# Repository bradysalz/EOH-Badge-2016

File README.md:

# EOH-Badge-2016
Badges made to hand out as a teaching exercise for the IEEE UIUC exhibit at Engineering Open House 2016. When you cover up the light sensor, the badges play along and flash to "Hail to the Orange". You can see a video of the build in action [here](https://www.youtube.com/watch?v=S4cmx-UWJ_Q&feature=youtu.be). This exhibit won second place in the "Just for Fun" category!

Special thanks to [David Mellis](http://web.media.mit.edu/~mellis/) for his [attiny library](https://github.com/damellis/attiny).

# Media

You can see a video of the exhibit in action, as well as IEEE's other exhibits [here](https://www.youtube.com/watch?v=S4cmx-UWJ_Q&feature=youtu.be).

Some excellent photos taken by Ray Chan during EOH [here](https://photos.google.com/share/AF1QipN_tZymQB7QjqU8kMJ0lrtPr13E5zKEWU58SieGECw1yZU4zlcl4fVr3wqzv2gzeQ?key=Mm0zcS1icEtFYU44bktMVk84OHpqdEVZcEROZm53)

# Bugs
- Orange and Blue LED are labeled backwards, whoops!
- The 500kOhm resistor is far too large, 50k would be much better. Typo from reading the datasheet, just makes the devices extremely sensitive. 
- First note is always wrong, probably need to re-read Timer init code
- Lanyard hole is slightly too small, +5-10 mils would be better
- My initials are covered up the battery cover (this one was actually intended)

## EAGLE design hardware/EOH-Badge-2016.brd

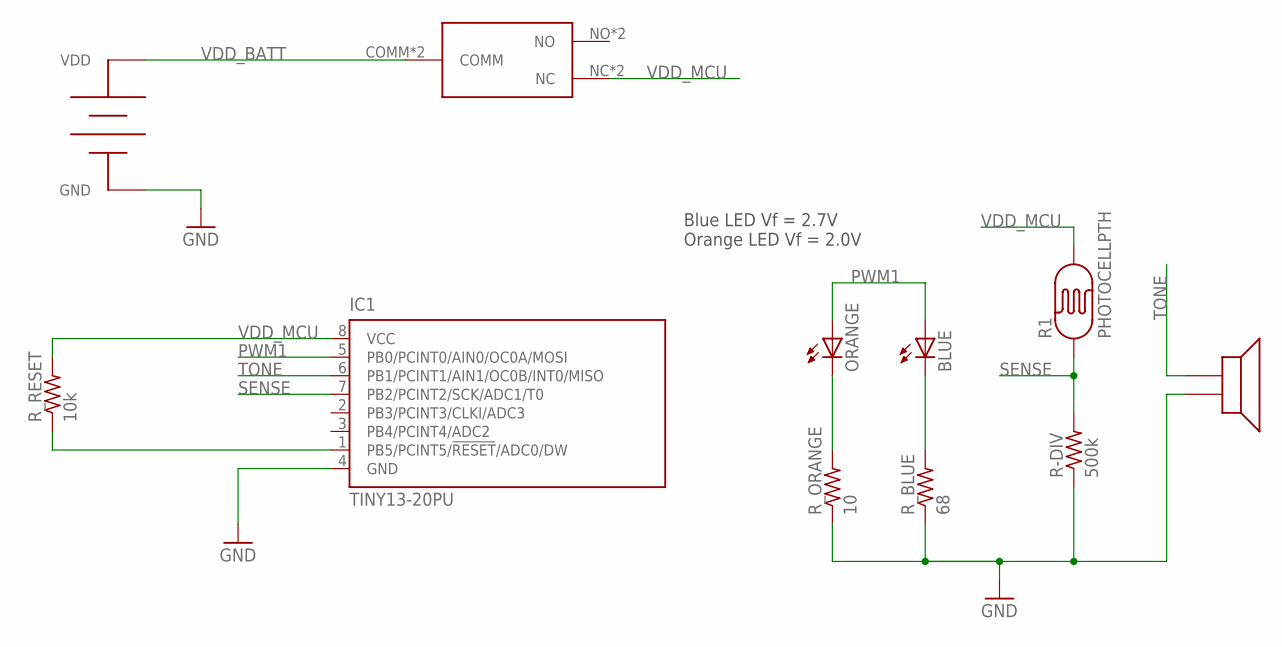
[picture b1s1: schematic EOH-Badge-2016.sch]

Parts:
BLUE: LED5MM
IC1: TINY13-20PU; DIL08
ORANGE: LED5MM
R1: PHOTOCELLPTH; PHOTOCELL
R-DIV: 500k; 0207/12
R_BLUE: 68; 0207/12
R_ORANGE: 10; 0207/12
R_RESET: 10k; 0207/12
U$1: MPD-BH32T-C; MPD-BC2032-E2
U$2: PIEZO; PS1240P02BT
U$3: EG1919-SW

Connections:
GND: IC1.4 (GND), R-DIV.1, R_BLUE.1, R_ORANGE.1, U$1.NEG (GND), U$2.GND
unnamed: IC1.1 (PB5/PCINT5/!RESET!/ADC0/DW), R_RESET.1
unnamed: ORANGE.K (C), R_ORANGE.2
unnamed: BLUE.K (C), R_BLUE.2
PWM1: BLUE.A, IC1.5 (PB0/PCINT0/AIN0/OC0A/MOSI), ORANGE.A
SENSE: IC1.7 (PB2/PCINT2/SCK/ADC1/T0), R1.1, R-DIV.2
TONE: IC1.6 (PB1/PCINT1/AIN1/OC0B/INT0/MISO), U$2.AUDIO
VDD_BATT: U$1.POS (VDD), U$3.COMM, U$3.COMM2 (COMM)
VDD_MCU: IC1.8 (VCC), R1.2, R_RESET.2, U$3.NC, U$3.NC2 (NC)

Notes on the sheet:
Blue LED Vf = 2.7V Orange LED Vf = 2.0V

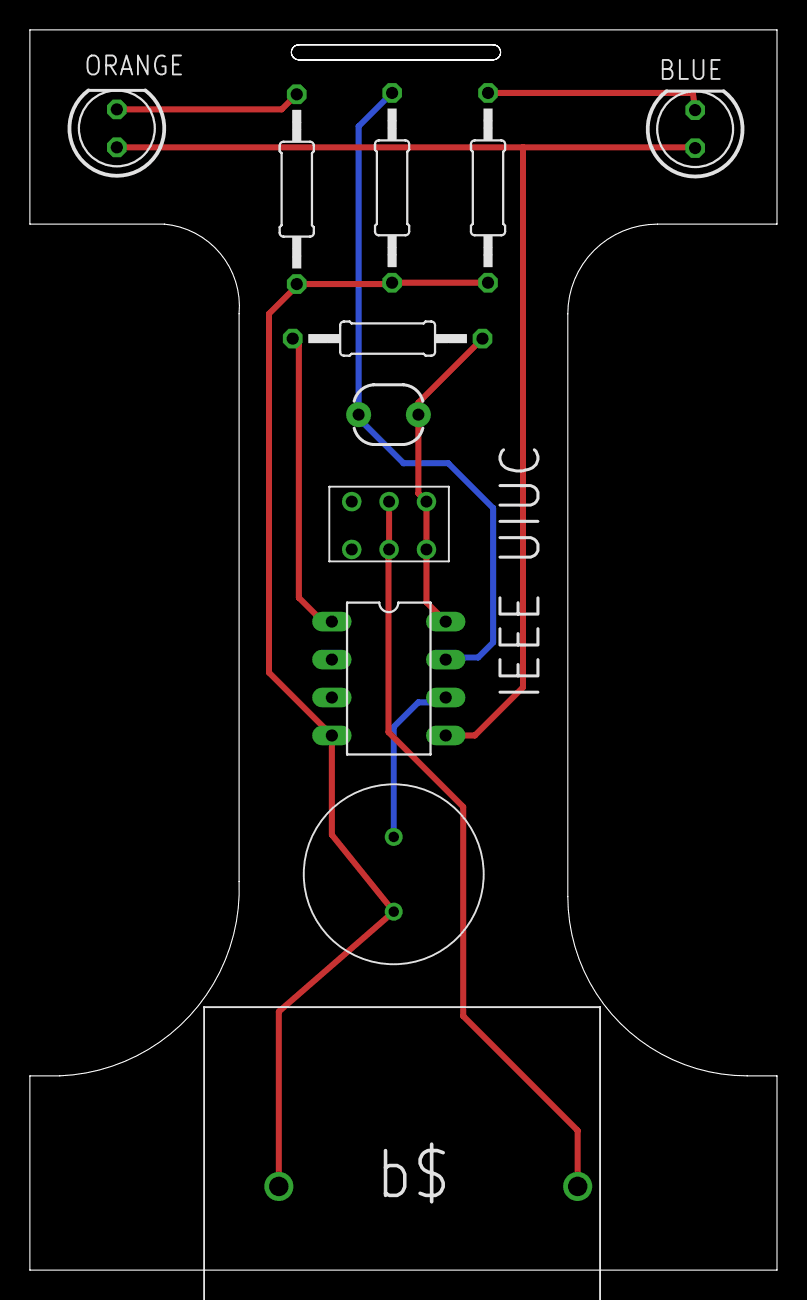
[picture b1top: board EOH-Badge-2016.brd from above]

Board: 2 copper layers, 50.0 x 83.0 mm, 11 parts (0 on the bottom side), 9 nets.

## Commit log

2016-03-22 Adding everything

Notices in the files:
parts and their libraries:
SparkFun-Sensors: Licensing: Creative Commons ShareAlike 4.0 International - https://creativecommons.org/licenses/by-sa/4.0
